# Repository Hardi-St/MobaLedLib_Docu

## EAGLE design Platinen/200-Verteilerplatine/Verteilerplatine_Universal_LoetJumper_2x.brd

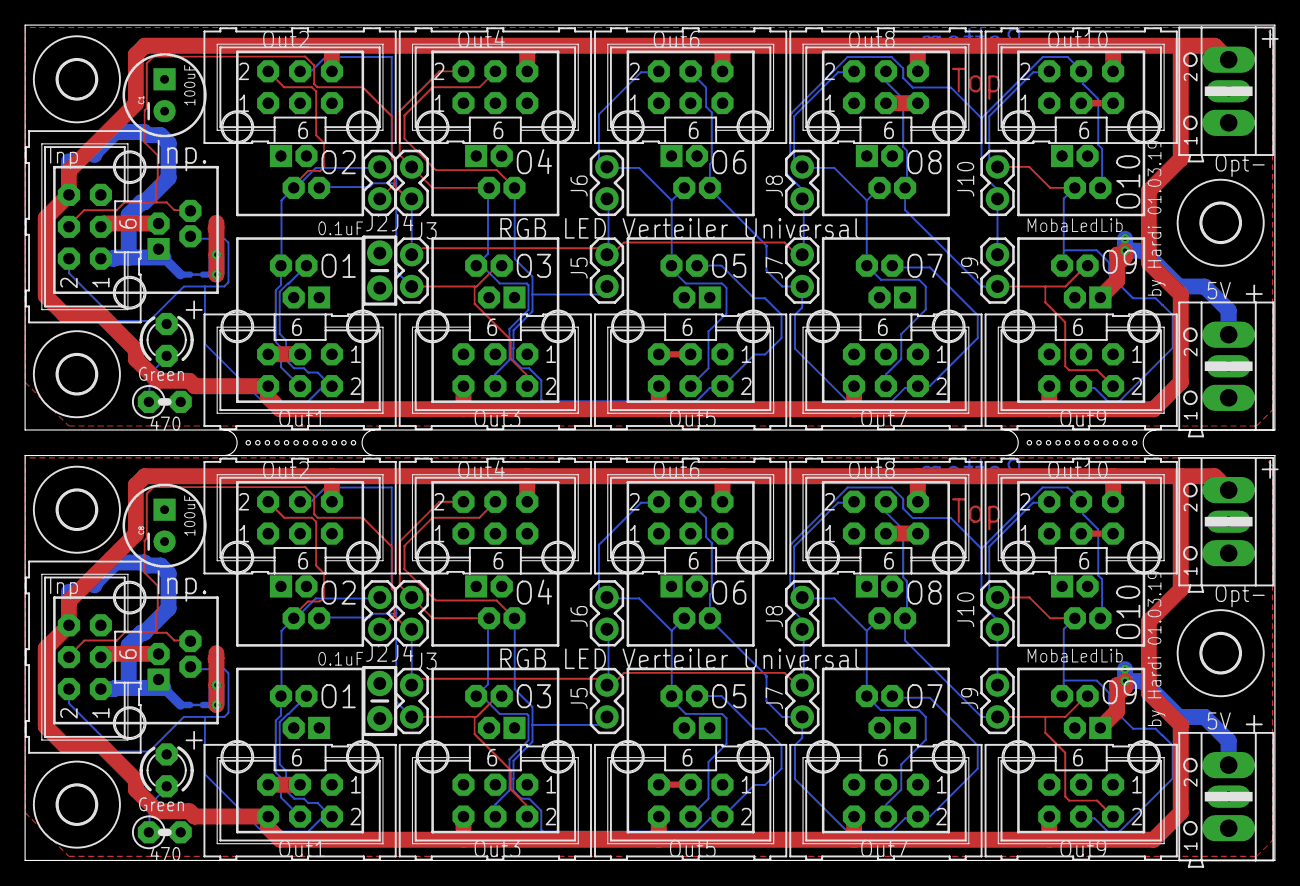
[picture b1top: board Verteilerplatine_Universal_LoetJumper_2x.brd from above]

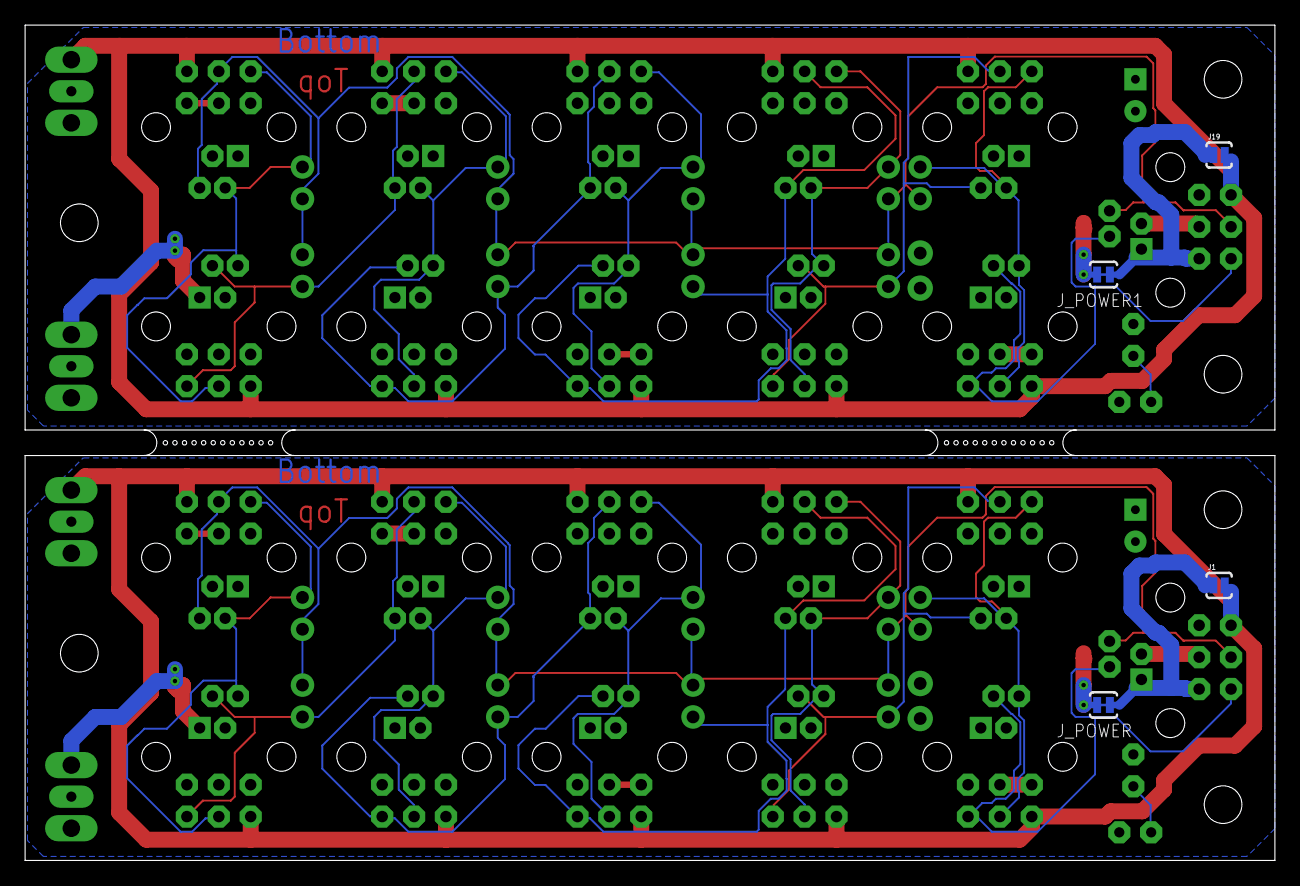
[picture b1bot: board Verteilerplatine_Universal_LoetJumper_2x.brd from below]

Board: 2 copper layers, 99.6 x 66.5 mm, 84 parts (4 on the bottom side), 32 nets.

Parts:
C1, C8: 100uF; SPARKFUN-CAPACITORS_CPOL-RADIAL-100UF-25V
C2, C9: 0.1uF; CAP-PTH-SMALL-KIT
H1, H2, H3, H5, H6, H8: MOUNT-HOLE3.0; 3,0
INP1, INP6: ML6
INP_, INP_1: RJ10
J1, J19: SOLDERJUMPERNO; SJ_2S-NO
J2, J3, J4, J5, J6, J7, J8, J9, J10, J11, J12, J13, J14, J15, J16, J17, J18, J20: SIG; 1X02
J_POWER, J_POWER1: SOLDERJUMPERTRACE; SJ_2S-TRACE
LED, LED1: Green; LED_LED3MM
O1, O2, O3, O4, O5, O6, O7, O8, O9, O10, O11, O12, O13, O14, O15, O16, O17, O18, O19, O20: ML6
OUT1, OUT2, OUT3, OUT4, OUT5, OUT6, OUT7, OUT8, OUT9, OUT10, OUT11, OUT12, OUT13, OUT14, OUT15, OUT16, OUT17, OUT18, OUT19, OUT20: RJ10
R1, R21: 470; RCL_0207/2V
X1, X2, X3, X4: AK500/2+M

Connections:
5V: C8.1, C9.2, J_POWER.1, LED.A, O1.1, O2.1, O3.1, O4.1, O5.1, O6.1, O7.1, O8.1, O9.1, O10.1, OUT1.1, OUT2.1, OUT3.1, OUT4.1, OUT5.1, OUT6.1, OUT7.1, OUT8.1, OUT9.1, OUT10.1, X2.2
5V1: C1.1, C2.2, J_POWER1.1, LED1.A, O11.1, O12.1, O13.1, O14.1, O15.1, O16.1, O17.1, O18.1, O19.1, O20.1, OUT11.1, OUT12.1, OUT13.1, OUT14.1, OUT15.1, OUT16.1, OUT17.1, OUT18.1, OUT19.1, OUT20.1, X3.2
GND: C8.2, C9.1, INP6.3, INP6.5, INP_.3, O1.3, O1.5, O2.3, O2.5, O3.3, O3.5, O4.3, O4.5, O5.3, O5.5, O6.3, O6.5, O7.3, O7.5, O8.3, O8.5, O9.3, O9.5, O10.3, O10.5, OUT1.3, OUT2.3, OUT3.3, OUT4.3, OUT5.3, OUT6.3, OUT7.3, OUT8.3, OUT9.3, OUT10.3, R21.2, X1.1, X1.M, X2.1, X2.M
GND1: C1.2, C2.1, INP1.3, INP1.5, INP_1.3, O11.3, O11.5, O12.3, O12.5, O13.3, O13.5, O14.3, O14.5, O15.3, O15.5, O16.3, O16.5, O17.3, O17.5, O18.3, O18.5, O19.3, O19.5, O20.3, O20.5, OUT11.3, OUT12.3, OUT13.3, OUT14.3, OUT15.3, OUT16.3, OUT17.3, OUT18.3, OUT19.3, OUT20.3, R1.2, X3.1, X3.M, X4.1, X4.M
unnamed: J10.2, O9.4, O10.2, OUT9.4, OUT10.2
unnamed: J7.2, O6.4, O7.2, OUT6.4, OUT7.2
unnamed: INP6.2, INP_.2, O1.2, OUT1.2
unnamed: J8.2, O7.4, O8.2, OUT7.4, OUT8.2
unnamed: J13.2, O13.4, O14.2, OUT14.4, OUT15.2
unnamed: J14.2, O14.4, O15.2, OUT15.4, OUT16.2
unnamed: INP6.1, INP_.1, J1.1, J_POWER.2
unnamed: J2.2, O1.4, O2.2, OUT1.4, OUT2.2
unnamed: J15.2, O15.4, O16.2, OUT16.4, OUT17.2
unnamed: INP1.4, INP_1.4, J11.1, J12.1, J13.1, J14.1, J15.1, J16.1, J17.1, J18.1, J20.1, O20.4, OUT12.4
unnamed: J3.2, O2.4, O3.2, OUT2.4, OUT3.2
unnamed: J18.2, O18.4, O19.2, OUT19.4, OUT20.2
unnamed: LED1.K, R1.1
unnamed: J11.2, O19.4, O20.2, OUT12.2, OUT20.4
unnamed: INP1.1, INP_1.1, J19.1, J_POWER1.2
unnamed: LED.K, R21.1
unnamed: J20.2, O11.2, O12.4, OUT11.4, OUT13.2
unnamed: J16.2, O16.4, O17.2, OUT17.4, OUT18.2
unnamed: J17.2, O17.4, O18.2, OUT18.4, OUT19.2
unnamed: INP1.2, INP_1.2, O12.2, OUT11.2
unnamed: J12.2, O11.4, O13.2, OUT13.4, OUT14.2
unnamed: J4.2, O3.4, O4.2, OUT3.4, OUT4.2
unnamed: J5.2, O4.4, O5.2, OUT4.4, OUT5.2
unnamed: J6.2, O5.4, O6.2, OUT5.4, OUT6.2
unnamed: INP6.4, INP_.4, J2.1, J3.1, J4.1, J5.1, J6.1, J7.1, J8.1, J9.1, J10.1, O10.4, OUT10.4
unnamed: J9.2, O8.4, O9.2, OUT8.4, OUT9.2
POWER1: INP1.6, J19.2, O11.6, O12.6, O13.6, O14.6, O15.6, O16.6, O17.6, O18.6, O19.6, O20.6, X4.2
POWER2: INP6.6, J1.2, O1.6, O2.6, O3.6, O4.6, O5.6, O6.6, O7.6, O8.6, O9.6, O10.6, X1.2

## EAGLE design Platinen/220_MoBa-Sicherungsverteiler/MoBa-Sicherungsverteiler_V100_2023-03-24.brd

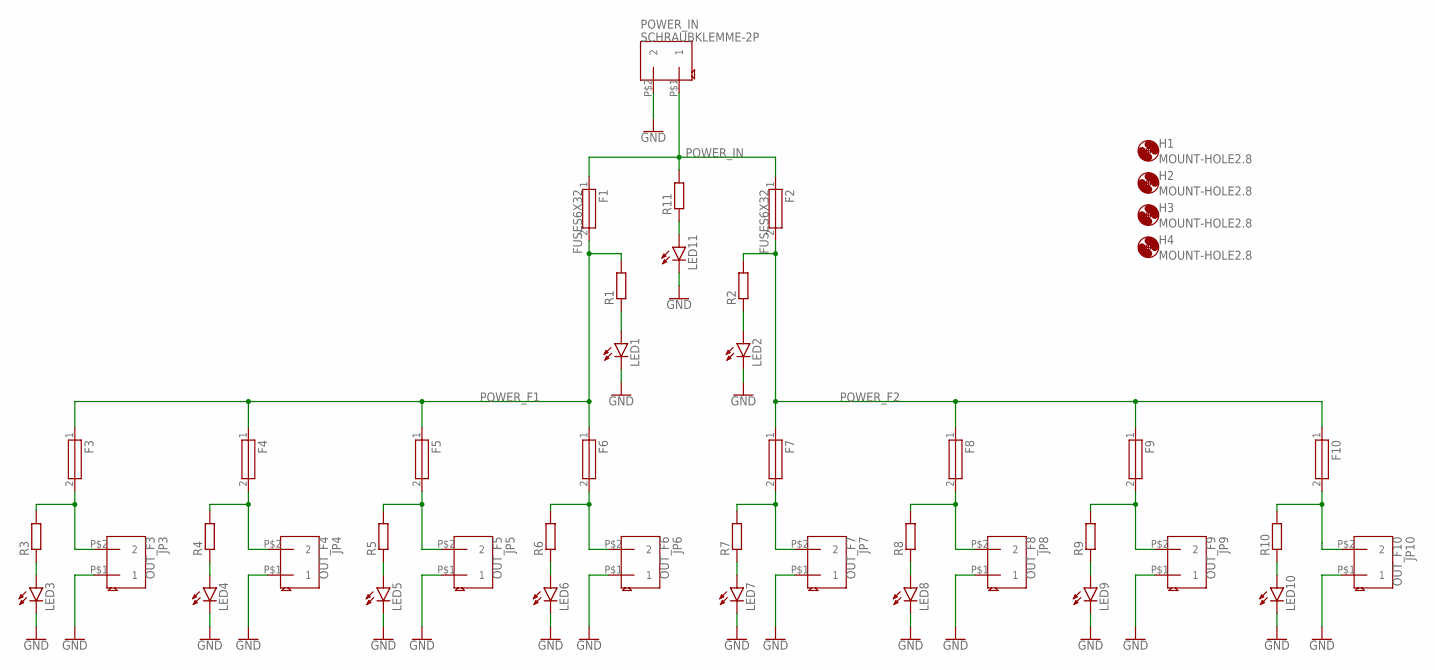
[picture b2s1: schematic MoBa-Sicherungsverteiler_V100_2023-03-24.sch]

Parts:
F1, F2: FUSES6X32; FUSE_6X32
F3, F4, F5, F6, F7, F8, F9, F10: FUSES5X20; FUSE_5X20
H1, H2, H3, H4: MOUNT-HOLE2.8; 2,8
JP3: OUT_F3; TERM-2P_508
JP4: OUT_F4; TERM-2P_508
JP5: OUT_F5; TERM-2P_508
JP6: OUT_F6; TERM-2P_508
JP7: OUT_F7; TERM-2P_508
JP8: OUT_F8; TERM-2P_508
JP9: OUT_F9; TERM-2P_508
JP10: OUT_F10; TERM-2P_508
LED1, LED2, LED3, LED4, LED5, LED6, LED7, LED8, LED9, LED10, LED11: LED3MM
POWER_IN: SCHRAUBKLEMME-2P; TERM-2P_508
R1, R2, R3, R4, R5, R6, R7, R8, R9, R10, R11: R-EU_0207/10; 0207/10

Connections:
GND: JP3.P$1 (1), JP4.P$1 (1), JP5.P$1 (1), JP6.P$1 (1), JP7.P$1 (1), JP8.P$1 (1), JP9.P$1 (1), JP10.P$1 (1), LED1.K (C), LED2.K (C), LED3.K (C), LED4.K (C), LED5.K (C), LED6.K (C), LED7.K (C), LED8.K (C), LED9.K (C), LED10.K (C), LED11.K (C), POWER_IN.P$2 (2)
unnamed: LED8.A, R8.1
unnamed: LED11.A, R11.1
POWER_F1: F1.2, F3.1, F4.1, F5.1, F6.1, R1.2
POWER_F2: F2.2, F7.1, F8.1, F9.1, F10.1, R2.2
POWER_F3: F3.2, JP3.P$2 (2), R3.2
POWER_F4: F4.2, JP4.P$2 (2), R4.2
POWER_F5: F5.2, JP5.P$2 (2), R5.2
POWER_F6: F6.2, JP6.P$2 (2), R6.2
POWER_F7: F7.2, JP7.P$2 (2), R7.2
POWER_F8: F8.2, JP8.P$2 (2), R8.2
POWER_F9: F9.2, JP9.P$2 (2), R9.2
POWER_F10: F10.2, JP10.P$2 (2), R10.2
POWER_IN: F1.1, F2.1, POWER_IN.P$1 (1), R11.2
RL1: LED1.A, R1.1
RL2: LED2.A, R2.1
RL3: LED3.A, R3.1
RL4: LED4.A, R4.1
RL5: LED5.A, R5.1
RL6: LED6.A, R6.1
RL7: LED7.A, R7.1
RL9: LED9.A, R9.1
RL10: LED10.A, R10.1

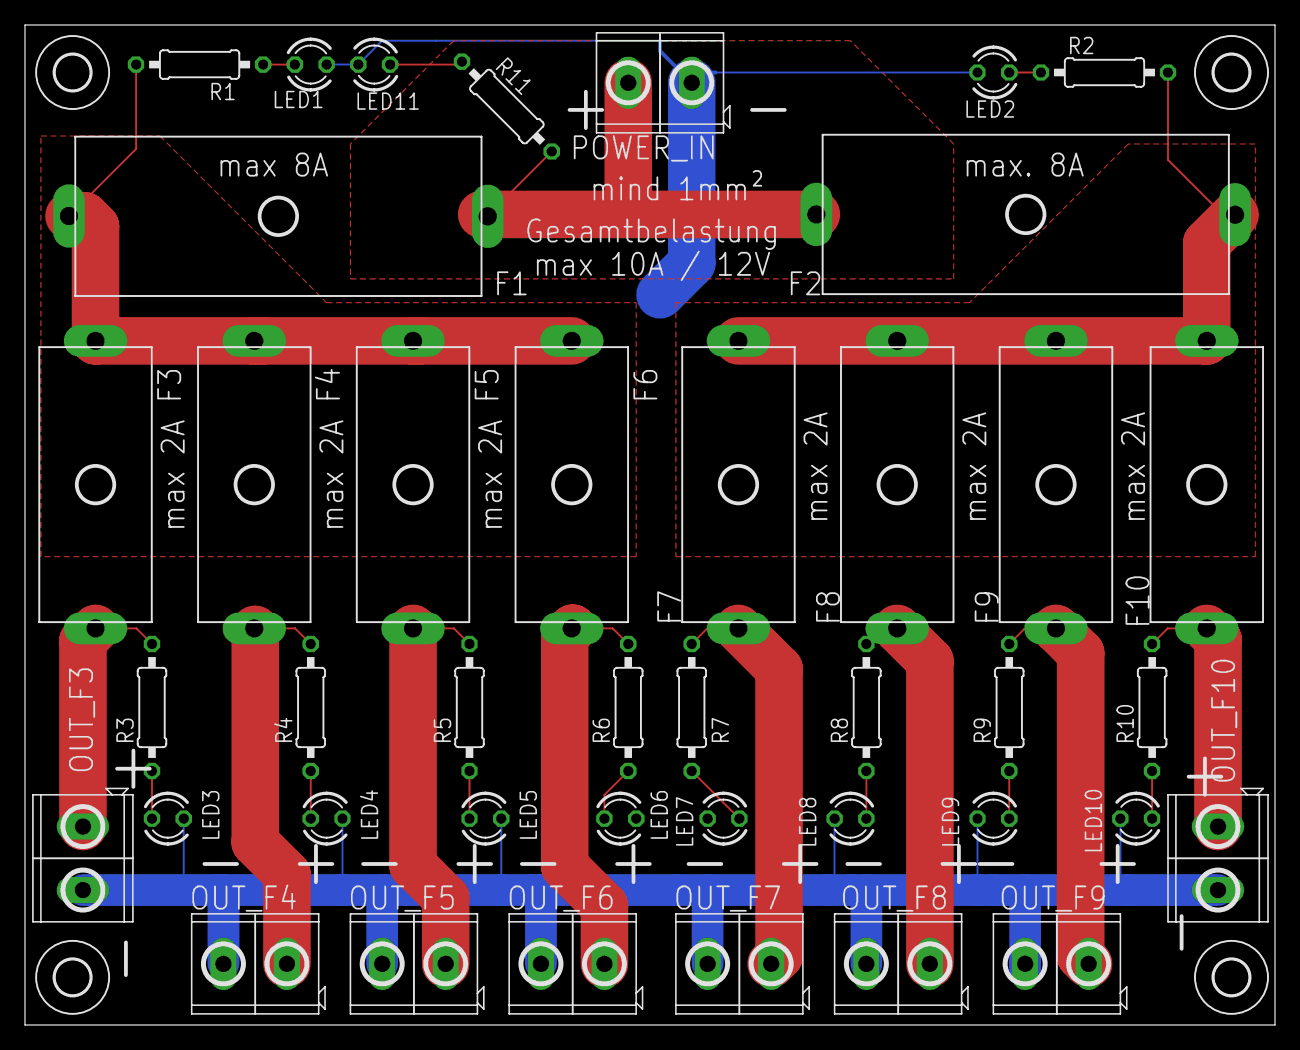
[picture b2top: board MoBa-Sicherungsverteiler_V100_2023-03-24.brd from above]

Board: 2 copper layers, 100.0 x 80.0 mm, 45 parts (0 on the bottom side), 23 nets.

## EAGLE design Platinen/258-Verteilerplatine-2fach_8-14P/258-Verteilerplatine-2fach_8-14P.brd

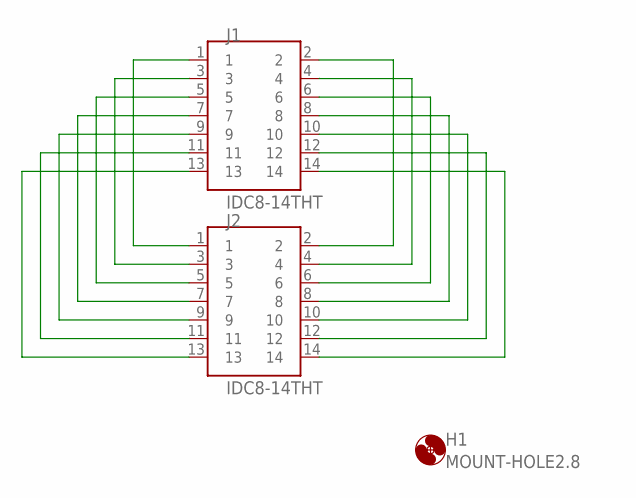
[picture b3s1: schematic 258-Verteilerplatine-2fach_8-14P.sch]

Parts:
H1: MOUNT-HOLE2.8; 2,8
J1, J2: IDC8-14THT; IDC8-14

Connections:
unnamed: J1.1, J2.1
unnamed: J1.3, J2.3
unnamed: J1.5, J2.5
unnamed: J1.7, J2.7
unnamed: J1.9, J2.9
unnamed: J1.11, J2.11
unnamed: J1.13, J2.13
unnamed: J1.2, J2.2
unnamed: J1.4, J2.4
unnamed: J1.6, J2.6
unnamed: J1.8, J2.8
unnamed: J1.10, J2.10
unnamed: J1.12, J2.12
unnamed: J1.14, J2.14

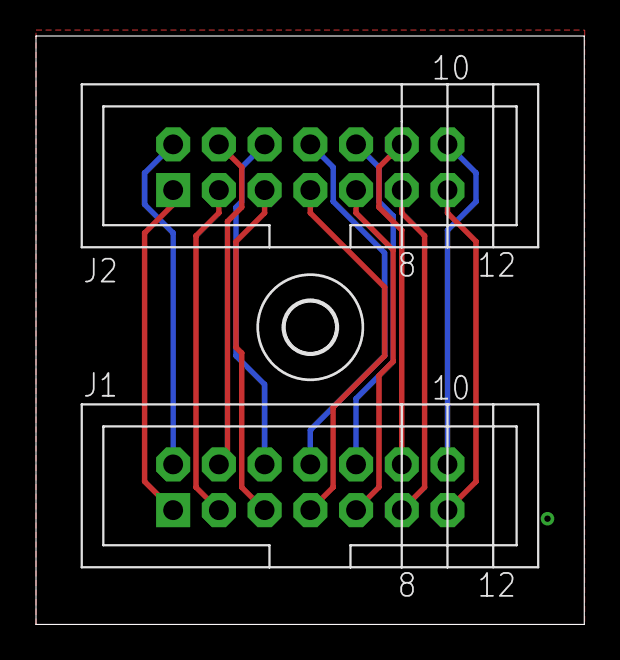
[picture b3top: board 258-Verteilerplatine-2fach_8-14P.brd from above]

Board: 2 copper layers, 30.5 x 32.7 mm, 3 parts (0 on the bottom side), 14 nets.

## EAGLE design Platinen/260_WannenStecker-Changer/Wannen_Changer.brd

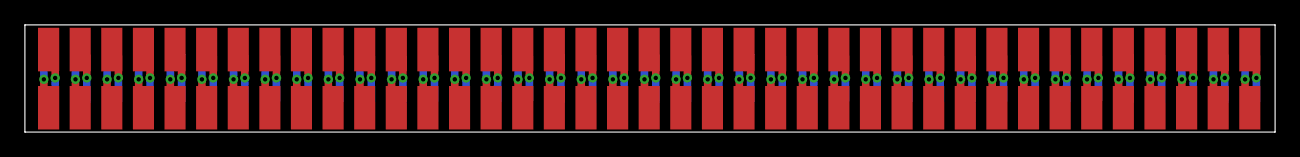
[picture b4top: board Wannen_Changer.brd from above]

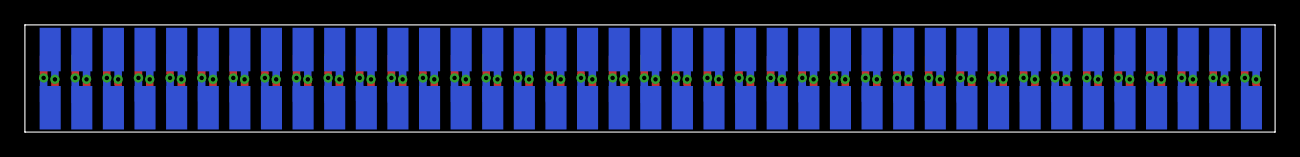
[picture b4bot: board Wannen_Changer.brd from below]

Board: 2 copper layers, 100.5 x 8.6 mm, 78 parts (39 on the bottom side), 78 nets.

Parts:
X1, X2, X3, X4, X5, X6, X7, X8, X9, X10, X11, X12, X13, X14, X15, X16, X17, X18, X19, X20, X21, X22, X23, X24, X25, X26, X27, X28, X29, X30, X31, X32, X33, X34, X35, X36, X37, X38, X39, X40, X41, X42, X43, X44, X45, X46, X47, X48, X49, X50, X51, X52, X53, X54, X55, X56, X57, X58, X59, X60, X61, X62, X63, X64, X65, X66, X67, X68, X69, X70, X71, X72, X73, X74, X75, X76, X77, X78: WANNE_D

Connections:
unnamed: X1.1, X2.1
unnamed: X1.2, X2.2
unnamed: X3.1, X4.1
unnamed: X3.2, X4.2
unnamed: X5.1, X6.1
unnamed: X5.2, X6.2
unnamed: X7.1, X8.1
unnamed: X7.2, X8.2
unnamed: X9.1, X10.1
unnamed: X9.2, X10.2
unnamed: X11.1, X12.1
unnamed: X11.2, X12.2
unnamed: X13.1, X14.1
unnamed: X13.2, X14.2
unnamed: X15.1, X16.1
unnamed: X15.2, X16.2
unnamed: X17.1, X18.1
unnamed: X17.2, X18.2
unnamed: X19.1, X20.1
unnamed: X19.2, X20.2
unnamed: X21.1, X22.1
unnamed: X21.2, X22.2
unnamed: X23.1, X24.1
unnamed: X23.2, X24.2
unnamed: X25.1, X26.1
unnamed: X25.2, X26.2
unnamed: X27.1, X28.1
unnamed: X27.2, X28.2
unnamed: X29.1, X30.1
unnamed: X29.2, X30.2
unnamed: X31.1, X32.1
unnamed: X31.2, X32.2
unnamed: X33.1, X34.1
unnamed: X33.2, X34.2
unnamed: X35.1, X36.1
unnamed: X35.2, X36.2
unnamed: X37.1, X38.1
unnamed: X37.2, X38.2
unnamed: X39.1, X40.1
unnamed: X39.2, X40.2
unnamed: X41.1, X42.1
unnamed: X41.2, X42.2
unnamed: X43.1, X44.1
unnamed: X43.2, X44.2
unnamed: X45.1, X46.1
unnamed: X45.2, X46.2
unnamed: X47.1, X48.1
unnamed: X47.2, X48.2
unnamed: X49.1, X50.1
unnamed: X49.2, X50.2
unnamed: X51.1, X52.1
unnamed: X51.2, X52.2
unnamed: X53.1, X54.1
unnamed: X53.2, X54.2
unnamed: X55.1, X56.1
unnamed: X55.2, X56.2
unnamed: X57.1, X58.1
unnamed: X57.2, X58.2
unnamed: X59.1, X60.1
unnamed: X59.2, X60.2
unnamed: X61.1, X62.1
unnamed: X61.2, X62.2
unnamed: X63.1, X64.1
unnamed: X63.2, X64.2
unnamed: X65.1, X66.1
unnamed: X65.2, X66.2
unnamed: X67.1, X68.1
unnamed: X67.2, X68.2
unnamed: X69.1, X70.1
unnamed: X69.2, X70.2
unnamed: X71.1, X72.1
unnamed: X71.2, X72.2
unnamed: X73.1, X74.1
unnamed: X73.2, X74.2
unnamed: X75.1, X76.1
unnamed: X75.2, X76.2
unnamed: X77.1, X78.1
unnamed: X77.2, X78.2

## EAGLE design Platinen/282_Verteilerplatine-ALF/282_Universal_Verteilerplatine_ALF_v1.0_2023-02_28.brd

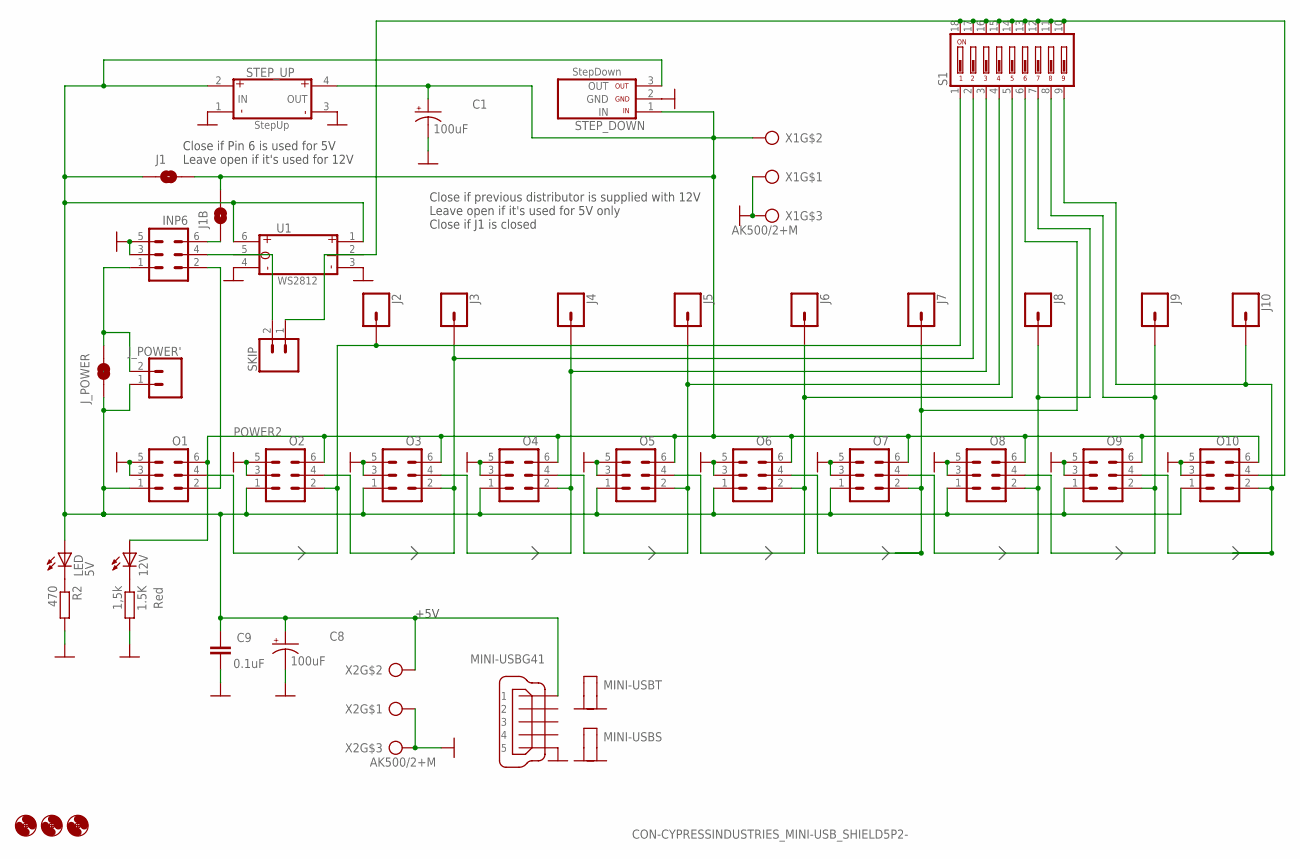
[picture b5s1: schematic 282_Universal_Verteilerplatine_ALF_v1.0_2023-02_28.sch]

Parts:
1.5K: 1,5k; RCL_0207/7
12V: Red; LED_LED3MM
C1, C8: 100uF; SPARKFUN-CAPACITORS_CPOL-RADIAL-100UF-25V
C9: 0.1uF; C025-025X050
H5, H6, H8: MOUNT-HOLE3.0; 3,0
INP6: ML6
J1, J1B: SOLDERJUMPERNO; SJ_2S-NO
J2, J3, J4, J5, J6, J7, J8, J9, J10: CONN_01_NO_BORDER; 1X01_NO_BORDER
J_POWER: SOLDERJUMPERNO; SJ_2S-NO
J_POWER': CONN_02; 1X02
LED: 5V; LED_LED3MM
MINI-USB: CON-CYPRESSINDUSTRIES_MINI-USB_SHIELD5P2-; MINI_USB_MULTI
O1, O2, O3, O4, O5, O6, O7, O8, O9, O10: ML6
R2: 470; RCL_0207/7
S1: DIP09YL
SKIP: CONN_02; 1X02
STEP_DOWN: STEP_DOWN; MINI_STEP_DOWN
STEP_UP: STEP_UP; MINI_STEP_UP
U1: WS2812_BREAKOUTCUT; WS2812__BREAKOUT_CUT
X1, X2: AK500/2+M

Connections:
5V: C8.1 (+), C9.2, J1.1, J_POWER.1, J_POWER'.1, LED.A, MINI-USB.1, O1.1, O2.1, O3.1, O4.1, O5.1, O6.1, O7.1, O8.1, O9.1, O10.1, STEP_DOWN.3 (VDD_OUT), STEP_UP.2 (VDD_IN), U1.1 (VDD1), U1.6 (VDD), X2.2
GND: 1.5K.2, C1.2 (-), C8.2 (-), C9.1, INP6.3, INP6.5, MINI-USB.5, MINI-USB.M1 (S1), MINI-USB.M2 (S2), MINI-USB.M3 (S1), MINI-USB.M4 (S2), O1.3, O1.5, O2.3, O2.5, O3.3, O3.5, O4.3, O4.5, O5.3, O5.5, O6.3, O6.5, O7.3, O7.5, O8.3, O8.5, O9.3, O9.5, O10.3, O10.5, R2.2, STEP_DOWN.2 (GND), STEP_UP.1 (GND_IN), STEP_UP.3 (GND_OUT), U1.3 (GND1), U1.4 (GND), X1.1, X1.M, X2.1, X2.M
unnamed: 1.5K.1, 12V.K (C)
unnamed: J7.1, O6.4, O7.2, S1.6
unnamed: INP6.2, O1.2
unnamed: J8.1, O7.4, O8.2, S1.7
unnamed: INP6.6, J1B.1
unnamed: INP6.4, SKIP.2, U1.5 (DO)
unnamed: O10.4, S1.10, S1.11, S1.12, S1.13, S1.14, S1.15, S1.16, S1.17, S1.18, SKIP.1, U1.2 (DIN)
unnamed: J2.1, O1.4, O2.2, S1.1
unnamed: INP6.1, J_POWER.2, J_POWER'.2
unnamed: J10.1, O9.4, O10.2, S1.9
unnamed: J3.1, O2.4, O3.2, S1.2
unnamed: LED.K (C), R2.1
unnamed: J4.1, O3.4, O4.2, S1.3
unnamed: J5.1, O4.4, O5.2, S1.4
unnamed: J6.1, O5.4, O6.2, S1.5
unnamed: J9.1, O8.4, O9.2, S1.8
POWER2: 12V.A, C1.1 (+), J1.2, J1B.2, O1.6, O2.6, O3.6, O4.6, O5.6, O6.6, O7.6, O8.6, O9.6, O10.6, STEP_DOWN.1 (VDD_IN), STEP_UP.4 (VDD_OUT), X1.2

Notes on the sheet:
+5V
Close if Pin 6 is used for 5V Leave open if it's used for 12V
Close if previous distributor is supplied with 12V Leave open if it's used for 5V only Close if J1 is closed

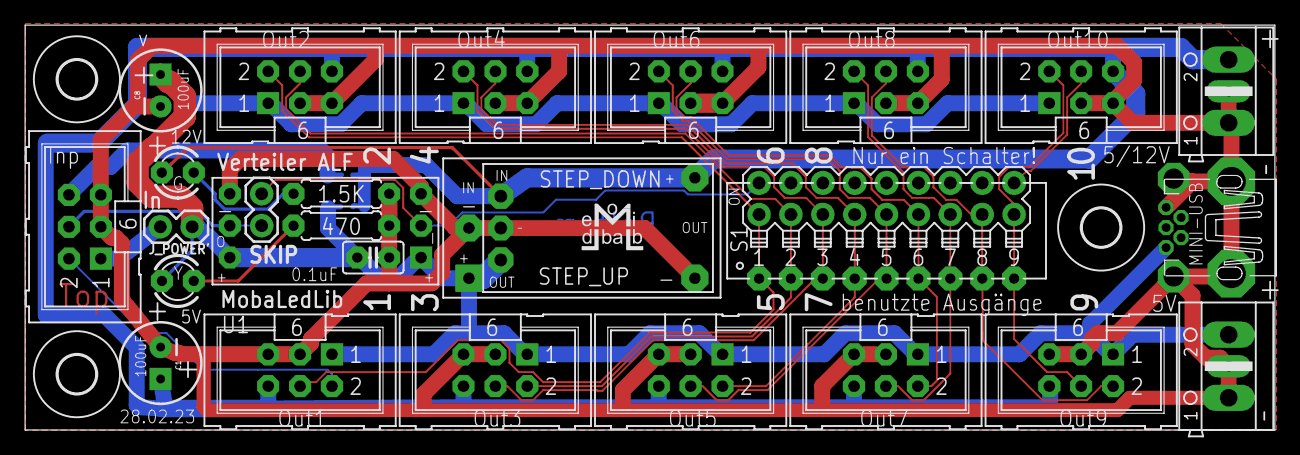
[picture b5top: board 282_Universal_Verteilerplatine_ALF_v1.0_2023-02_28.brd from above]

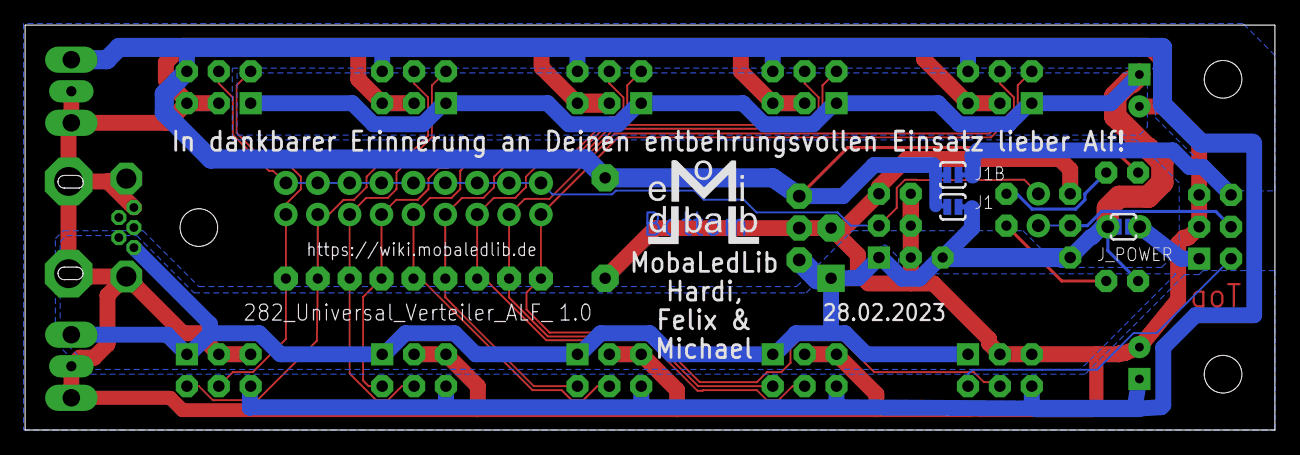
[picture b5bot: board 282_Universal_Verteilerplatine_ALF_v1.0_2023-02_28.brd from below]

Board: 2 copper layers, 99.6 x 32.3 mm, 42 parts (3 on the bottom side), 19 nets.

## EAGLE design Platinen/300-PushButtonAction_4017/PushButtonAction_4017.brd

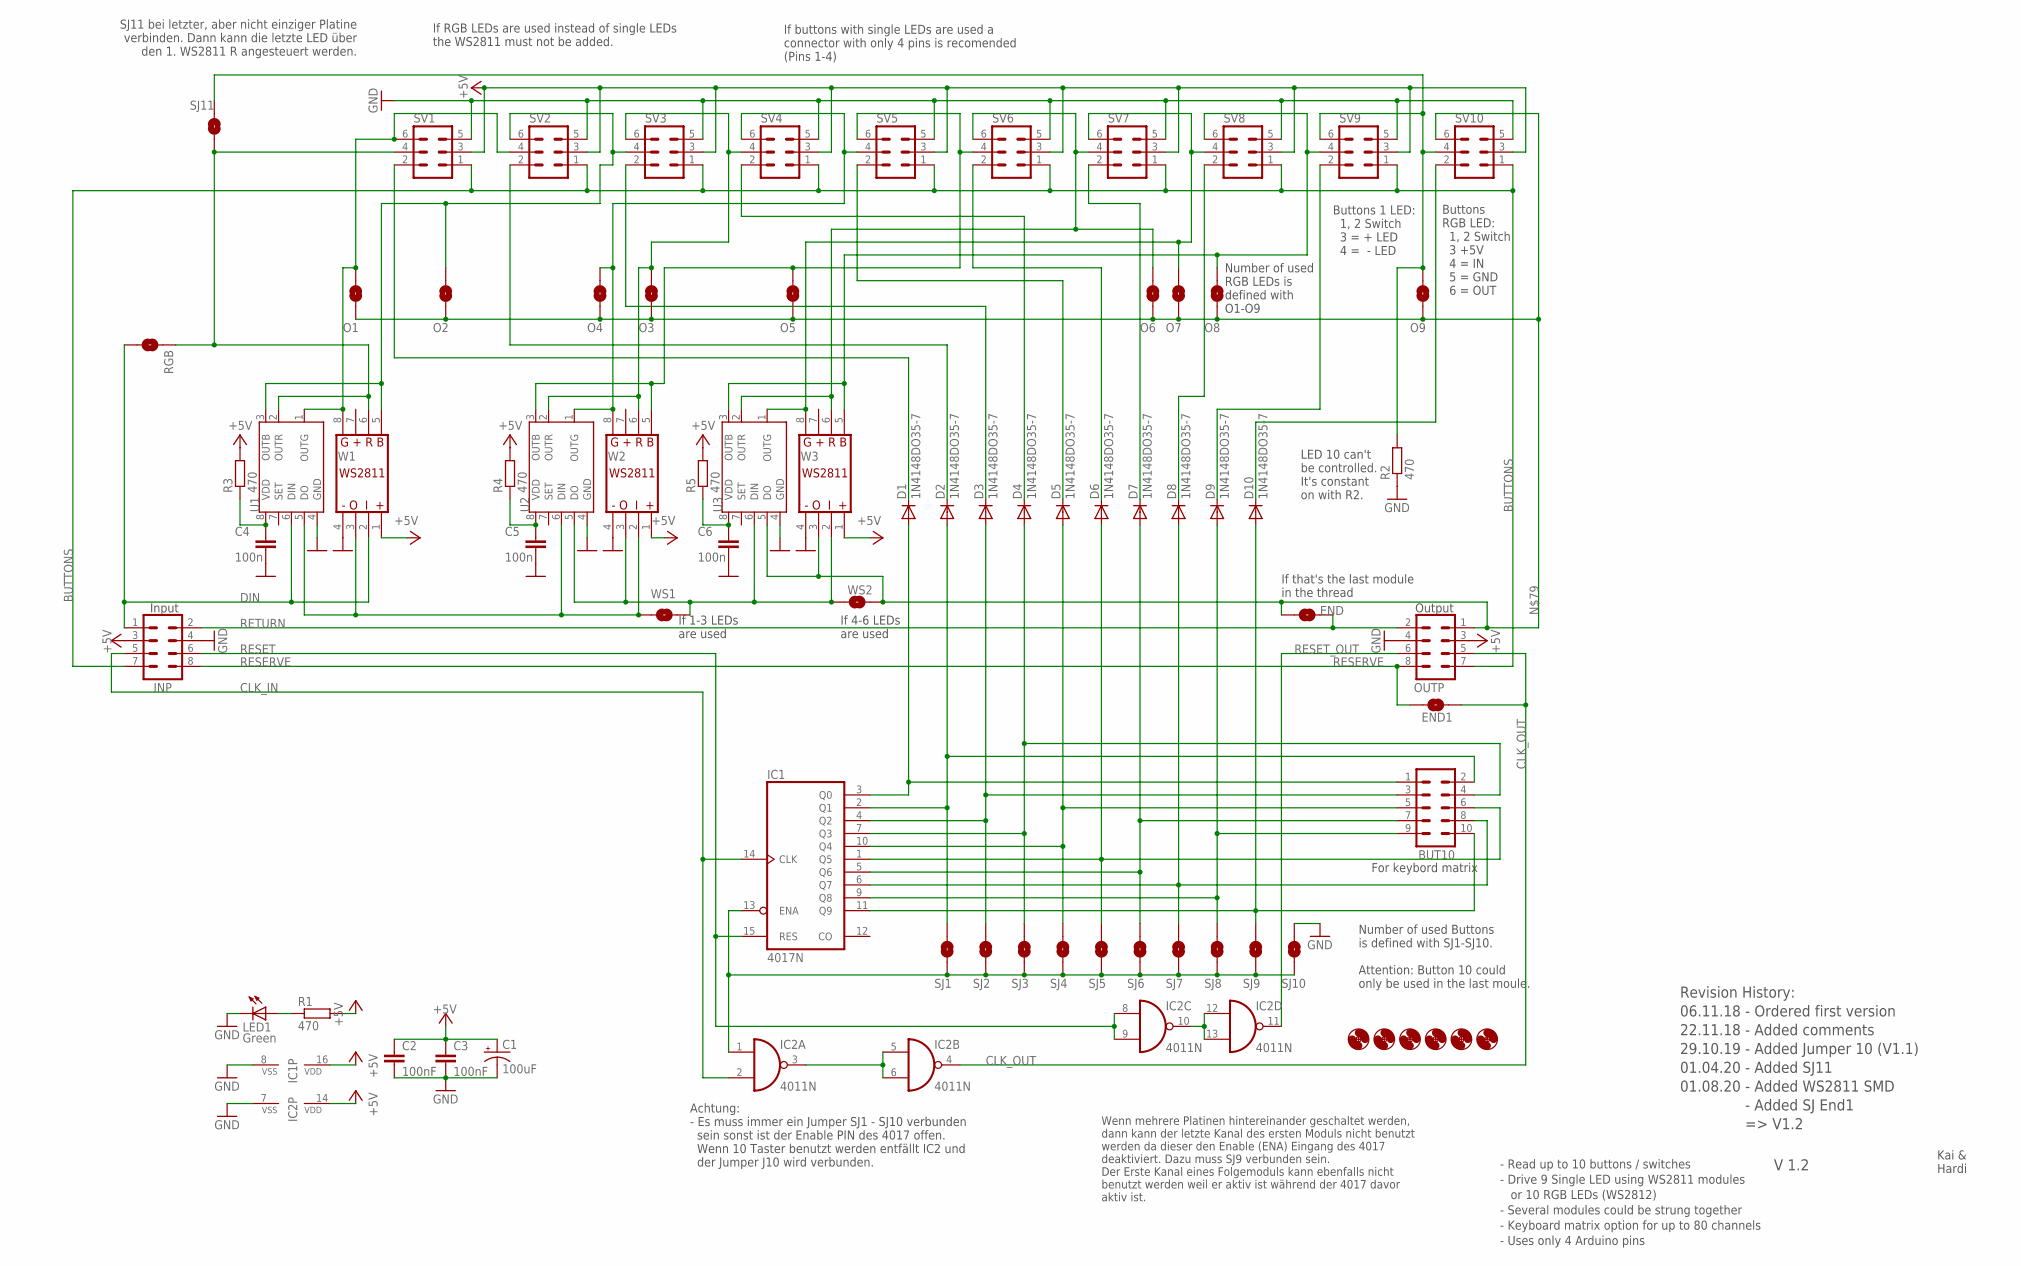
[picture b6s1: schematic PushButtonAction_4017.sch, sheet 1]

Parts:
BUT10: CON-HARTING-ML_ML10
C1: 100uF; CPOL-RADIAL-100UF-25V
C2, C3: 100nF; CAP-PTH-SMALL-KIT
C4, C5, C6: 100n; C025-024X044
D1, D2, D3, D4, D5, D6, D7, D8, D9, D10: 1N4148DO35-7; DO35-7
END, END1: SOLDERJUMPERNO; SJ_2S-NO
H1, H2, H3, H4, H5, H6: MOUNT-HOLE3.0; 3,0
IC1: 4017N; DIL16
IC2: 4011N; DIL14
INP: CON-HARTING-ML_ML08
LED1: Green; LED3MM
O1, O2, O3, O4, O5, O6, O7, O8, O9: SOLDERJUMPERNO; SJ_2S-NO
OUTP: CON-HARTING-ML_ML08
R1, R3, R4, R5: 470; 0207/2V
R2: 470; 0204/5
RGB: SOLDERJUMPERNO; SJ_2S-NO
SJ1, SJ2, SJ3, SJ4, SJ5, SJ6, SJ7, SJ8, SJ9, SJ10, SJ11: SOLDERJUMPERNO; SJ_2S-NO
SV1, SV2, SV3, SV4, SV5, SV6, SV7, SV8, SV9, SV10: CON-HARTING-ML_ML6
U1, U2, U3: S3PO_MODUL_WS2811_SOUND_MP3-TF-16P_WS2811_AND_ATT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; SOP8
W1, W2, W3: WS28115V; WS2811_WS2811_5V
WS1, WS2: SOLDERJUMPERNO; SJ_2S-NO

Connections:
+5V: C1.1 (+), C2.1, C3.1, IC1.16 (VDD), IC2.14 (VDD), INP.3, OUTP.3, R1.2, R3.2, R4.2, R5.2, SV1.3, SV2.3, SV3.3, SV4.3, SV5.3, SV6.3, SV7.3, SV8.3, SV9.3, SV10.3, W1.1, W2.1, W3.1
BUTTONS: INP.7, OUTP.7, SV1.1, SV2.1, SV3.1, SV4.1, SV5.1, SV6.1, SV7.1, SV8.1, SV9.1, SV10.1
CLK_IN: IC1.14 (CLK), IC2.2 (I1), INP.5
CLK_OUT: END1.1, IC2.4 (O), OUTP.5
DIN: INP.1, RGB.1, U1.6 (DIN), W1.2
GND: C1.2 (-), C2.2, C3.2, C4.2, C5.2, C6.2, IC1.8 (VSS), IC2.7 (VSS), INP.4, LED1.K (C), OUTP.4, R2.1, SJ10.2, SV1.5, SV2.5, SV3.5, SV4.5, SV5.5, SV6.5, SV7.5, SV8.5, SV9.5, SV10.5, U1.4 (GND), U2.4 (GND), U3.4 (GND), W1.4, W2.4, W3.4
unnamed: IC2.3 (O), IC2.5 (I0), IC2.6 (I1)
unnamed: IC1.13 (ENA), IC2.1 (I0), SJ1.1, SJ2.1, SJ3.1, SJ4.1, SJ5.1, SJ6.1, SJ7.1, SJ8.1, SJ9.1, SJ10.1
unnamed: IC2.10 (O), IC2.12 (I0), IC2.13 (I1)
unnamed: RGB.2, SJ11.2, SV1.4, U1.2 (OUTR), W1.6
unnamed: BUT10.10, D10.A, IC1.11 (Q9), SJ9.2
unnamed: D1.C, SV1.2
unnamed: U1.5 (DO), U2.6 (DIN), W1.3, W2.2, WS1.1
unnamed: O5.2, SV5.6, SV6.4, U2.3 (OUTB), W2.5
unnamed: D2.C, SV2.2
unnamed: D3.C, SV3.2
unnamed: BUT10.2, D2.A, IC1.2 (Q1), SJ1.2
unnamed: BUT10.3, D3.A, IC1.4 (Q2), SJ2.2
unnamed: BUT10.4, D4.A, IC1.7 (Q3), SJ3.2
unnamed: BUT10.5, D5.A, IC1.10 (Q4), SJ4.2
unnamed: BUT10.6, D6.A, IC1.1 (Q5), SJ5.2
unnamed: BUT10.7, D7.A, IC1.5 (Q6), SJ6.2
unnamed: BUT10.8, D8.A, IC1.6 (Q7), SJ7.2
unnamed: BUT10.9, D9.A, IC1.9 (Q8), SJ8.2
unnamed: D4.C, SV4.2
unnamed: D5.C, SV5.2
unnamed: LED1.A, R1.1
unnamed: U2.5 (DO), U3.6 (DIN), W2.3, W3.2, WS1.2, WS2.2
unnamed: D6.C, SV6.2
unnamed: D8.C, SV8.2
unnamed: D9.C, SV9.2
unnamed: D10.C, SV10.2
unnamed: BUT10.1, D1.A, IC1.3 (Q0)
unnamed: O1.2, SV1.6, SV2.4, U1.1 (OUTG), W1.8
unnamed: O2.2, SV2.6, SV3.4, U1.3 (OUTB), W1.5
unnamed: O4.2, SV4.6, SV5.4, U2.1 (OUTG), W2.8
unnamed: O3.2, SV3.6, SV4.4, U2.2 (OUTR), W2.6
unnamed: O6.2, SV6.6, SV7.4, U3.2 (OUTR), W3.6
unnamed: O7.2, SV7.6, SV8.4, U3.1 (OUTG), W3.8
unnamed: O8.2, SV8.6, SV9.4, U3.3 (OUTB), W3.5
unnamed: O9.2, R2.2, SJ11.1, SV9.6, SV10.4
unnamed: C4.1, R3.1, U1.8 (VDD)
unnamed: C5.1, R4.1, U2.8 (VDD)
unnamed: C6.1, R5.1, U3.8 (VDD)
unnamed: END.2, O1.1, O2.1, O3.1, O4.1, O5.1, O6.1, O7.1, O8.1, O9.1, OUTP.1, SV10.6, U3.5 (DO), W3.3, WS2.1
O6: D7.C, SV7.2
RESERVE: END1.2, INP.8, OUTP.8
RESET: IC1.15 (RES), IC2.8 (I0), IC2.9 (I1), INP.6
RESET_OUT: IC2.11 (O), OUTP.6
RETURN: END.1, INP.2, OUTP.2

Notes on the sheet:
Input
Output
Kai & Hardi
- Read up to 10 buttons / switches - Drive 9 Single LED using WS2811 modules or 10 RGB LEDs (WS2812) - Several modules could be strung together - Keyboard matrix option for up to 80 channels - Uses only 4 Arduino pins
For keybord matrix
If 1-3 LEDs are used
If 4-6 LEDs are used
If that's the last module in the thread
Number of used Buttons is defined with SJ1-SJ10. Attention: Button 10 could only be used in the last moule.
If RGB LEDs are used instead of single LEDs the WS2811 must not be added.
Number of used RGB LEDs is defined with O1-O9
If buttons with single LEDs are used a connector with only 4 pins is recomended (Pins 1-4)
Buttons 1 LED: 1, 2 Switch 3 = + LED 4 = - LED
Buttons RGB LED: 1, 2 Switch 3 +5V 4 = IN 5 = GND 6 = OUT
LED 10 can't be controlled. It's constant on with R2.
Achtung: - Es muss immer ein Jumper SJ1 - SJ10 verbunden sein sonst ist der Enable PIN des 4017 offen. Wenn 10 Taster benutzt werden entfällt IC2 und der Jumper J10 wird verbunden.
Wenn mehrere Platinen hintereinander geschaltet werden, dann kann der letzte Kanal des ersten Moduls nicht benutzt werden da dieser den Enable (ENA) Eingang des 4017 deaktiviert. Dazu muss SJ9 verbunden sein. Der Erste Kanal eines Folgemoduls kann ebenfalls nicht benutzt werden weil er aktiv ist wä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
Revision History: 06.11.18 - Ordered first version 22.11.18 - Added comments 29.10.19 - Added Jumper 10 (V1.1) 01.04.20 - Added SJ11 01.08.20 - Added WS2811 SMD - Added SJ End1 => V1.2
V 1.2
SJ11 bei letzter, aber nicht einziger Platine verbinden. Dann kann die letzte LED über den 1. WS2811 R angesteuert werden.

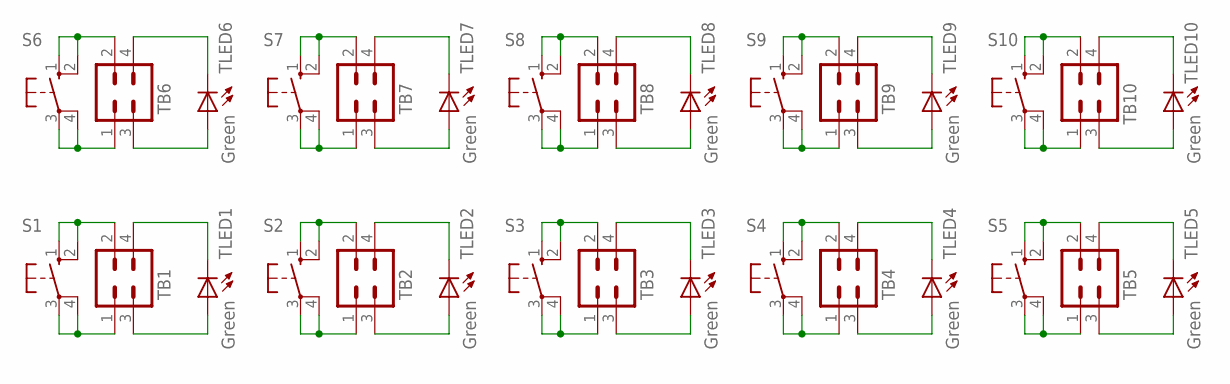
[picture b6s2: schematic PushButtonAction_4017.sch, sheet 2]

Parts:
S1, S2, S3, S4, S5, S6, S7, S8, S9, S10: 10-XX; B3F-10XX
TB1, TB2, TB3, TB4, TB5, TB6, TB7, TB8, TB9, TB10: CON-HARTING-ML_ML4ML4_FEMALE; ML_ML4_FEMALE
TLED1, TLED2, TLED3, TLED4, TLED5, TLED6, TLED7, TLED8, TLED9, TLED10: Green; LED_LED3MM

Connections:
unnamed: S1.1 (S), S1.2 (S1), TB1.2
unnamed: S1.3, S1.4 (P1), TB1.1
unnamed: TB1.3, TLED1.A
unnamed: TB1.4, TLED1.K (C)
unnamed: S2.1 (S), S2.2 (S1), TB2.2
unnamed: S2.3, S2.4 (P1), TB2.1
unnamed: TB2.3, TLED2.A
unnamed: TB2.4, TLED2.K (C)
unnamed: S3.1 (S), S3.2 (S1), TB3.2
unnamed: S3.3, S3.4 (P1), TB3.1
unnamed: TB3.3, TLED3.A
unnamed: TB3.4, TLED3.K (C)
unnamed: S4.1 (S), S4.2 (S1), TB4.2
unnamed: S4.3, S4.4 (P1), TB4.1
unnamed: TB4.3, TLED4.A
unnamed: TB4.4, TLED4.K (C)
unnamed: S5.1 (S), S5.2 (S1), TB5.2
unnamed: S5.3, S5.4 (P1), TB5.1
unnamed: TB5.3, TLED5.A
unnamed: TB5.4, TLED5.K (C)
unnamed: S6.1 (S), S6.2 (S1), TB6.2
unnamed: S6.3, S6.4 (P1), TB6.1
unnamed: TB6.3, TLED6.A
unnamed: TB6.4, TLED6.K (C)
unnamed: S7.1 (S), S7.2 (S1), TB7.2
unnamed: S7.3, S7.4 (P1), TB7.1
unnamed: TB7.3, TLED7.A
unnamed: TB7.4, TLED7.K (C)
unnamed: S8.1 (S), S8.2 (S1), TB8.2
unnamed: S8.3, S8.4 (P1), TB8.1
unnamed: TB8.3, TLED8.A
unnamed: TB8.4, TLED8.K (C)
unnamed: S9.1 (S), S9.2 (S1), TB9.2
unnamed: S9.3, S9.4 (P1), TB9.1
unnamed: TB9.3, TLED9.A
unnamed: TB9.4, TLED9.K (C)
unnamed: S10.1 (S), S10.2 (S1), TB10.2
unnamed: S10.3, S10.4 (P1), TB10.1
unnamed: TB10.3, TLED10.A
unnamed: TB10.4, TLED10.K (C)

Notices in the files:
parts and their libraries:
SparkFun-Capacitors: Licensing: Creative Commons ShareAlike 4.0 International - https://creativecommons.org/licenses/by-sa/4.0
